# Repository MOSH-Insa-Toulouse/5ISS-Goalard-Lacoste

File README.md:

# Microcontrollers & Open Source Hardware (M&OSH)
This repository contains all the work and related documents realised by Rémi and David as part of the "Microcontroller & Open Source Hardware" major.  
Here is what you can find in this file :
* Course objectives
* Project description
* Technical realisation
* Delivery
* Improvements
* Conclusion
  
## Course objectives
The main objective of this class is to provide a transversal perspective of the creation of an IoT system. From the solution proposal to the end of system design, we take a look at all the conception steps, trying to merge both the hardware and software requirements.

## Project desciption
This project is a multidisciplinary work built around the use of a gas sensor. The idea is the following : we conceived a gas sensor to monitor air quality, and now want to integrate it in on an electronic card (Arduino) to collect data from its environment, then send them over a low speed network.
This is an overview of the architecture :

As it is multidisciplinary, we divided the project in various steps : 
* Gas sensor conception
* Data communication via LoRa
* Hardware & PCB design

## Technical realisation
Let's look at the different steps of the project through the technical realisation point of view.

### Gas sensor conception
The gas sensor designed for monitoring air quality is composed of two sensing elements. Both are based on a combination of silicon substrate with tungsten trioxide nanoparticles, and allow to detect gas concentration regarding the variation of their conductivity. The sensor also integrate a temperature sensor, and only need a few mA to work.   

The sensor parts are described in the following schema :  

For all the sensor information, please refer to the [datasheet](https://github.com/patatorfr/5ISS-Goalard-Lacoste/blob/main/Datasheet/Datasheet.pdf).

The gas sensor was conceived in AIME in october, but we will use a commercial sensor in the next steps of the project for simplicity reasons.    

### Data communication via LoRa
Now we have a working sensor, we want to be able to send the retrieved data. To do so, we will use LoRa protocol and the gateway accessible at INSA via ChirpStack.
In order to achieve the communication, we need a few elements :
* Electonical card (Arduino UNO)
* LoRa communication module (RN2483), plugged to the UNO
* Gas sensor (MQ2), plugged to the UNO
  
First, we use the RN2483 datasheet and choose the pins to use to connect it to the Arduino UNO :

The chosen pins are welded, then the module is connected to the arduino using wires and a breadboard :

To send data using LoRa from the INSA, we have to use a gateway accessible through ChirpStack framework. We reuse an already existing Arduino code modified as follow :
* Connect to the gateway using our specific credentials
* Retrieve data measured by the gas sensor
* Encode data from the sensor as bytes
* Use 'TheThingsNetwork' library, that allows to send data to ChirpStack gateway as bytes

You can find the Arduino code [here](https://github.com/patatorfr/5ISS-Goalard-Lacoste/blob/main/Capteur_Gaz/Capteur_Gaz.ino).

Now the data from the gas sensor can be send out using the gateway, the last step is to make the emitted data accessible. To do it, we use Node-RED and retrieve the data sent from ChirpStack as MQTT packets. We therefore use a function to decode the received data, as ChirpStack send them using base 64, and post a text of the final value : 

To test our system, we displayed the value measured by the sensor in the Arduino IDE, and displayed the same value after getting it on Node-RED. We fortunately displayed twice the same value.

### Hardware & PCB design
In the previous part, we used a breadboard to connect the sensor to the Arduino. This is not an optimal solution, so we use KiCad to design a shield that can be directly plugged on the Arduino board.  

First, let's have a look at the various components of the shield :   

* Arduino UNO board :   
  Generic board provided by KiCad.
  
* Gas sensor :    
  We created a symbol for our manufactured gas sensor, using the 'Package_TO_SOT_THT:TO-5-10_Window' footprint.
  
* Gas type switch :     
  As the gas sensor is capable of measuring 2 different gases, we use a switch to choose the one we want the informations from. It is composed of 2 resistors and a MOSFET transistor. The choice of the gas measured is done via the GPIO n°2 of the Arduino UNO.
     
* LoRa connector :   
  We welded the LoRa module on a little PCB to have a better view/use of its pins. Therefore we just have to plug it on a connector to access the LoRa chip.
  
* Amplifier circuit :   
  This circuit is build based on LTC1050 operational amplifier, a few resistors and capacitors, and a variable resistor.
  
* Variable resistor :      
  As our sensor contains an intern heating resistor, we need to use a variable resistor to adapt the input current and assure it stay in the same range (not to low so the ADC can see it, but not too high so we don't kill the Arduino). The resistor is controlled 
  directly from the Arduino, which allows us to know the 'transformation' done to the current. Using it, we assure a proper functioning of the Arduino, and are still able to provide a good measurement of the gas concentration.

As the sensor resistance is huge, and it varies depending on the gas it measures and its concentration, the input current of the Arduino will be very low. To make it usable, we need to increase the current value, which will be done using an amplifier circuit.

 It is composed as follow :
 
* Low-pass filter for input current noise : R4 - C1
* Actif filter to reduce 50Hz noise : R3 - C4
* Output low-pass filter : R5 - C2
* [Gas sensor](https://github.com/patatorfr/5ISS-Goalard-Lacoste/blob/main/images/image8.png) : we create a component that represent it with the relation => I=V(cp,cn)*(10n+v(gc,gn)*10n)).

We use LTSpice to simulate the behavior of the system and find the cutoff frequency of each filter :

| Filter | Frequency |
|----------|----------|
| 1 [simulation](https://github.com/patatorfr/5ISS-Goalard-Lacoste/blob/main/images/16hz.png) | 16 Hz |
| 2 [simulation](https://github.com/patatorfr/5ISS-Goalard-Lacoste/blob/main/images/1.6hz.png) | 1.6 Hz |
| 3 [simulation](https://github.com/patatorfr/5ISS-Goalard-Lacoste/blob/main/images/1.6khz.png) | 1.6 kHz |

The second step is to build the PCB of the shield using these components. As we were supposed to use INSA's equipement to print the PCB, our constraint was to use only one layer.  

Here is the final version of our PCB :  

And the 3D view to have a better space representation of the PCB :  

## Delivery
A short explanation about the files you can find in the various subdirectories :
* Gas sensor datasheet [here](https://github.com/patatorfr/5ISS-Goalard-Lacoste/blob/main/Datasheet/Datasheet.pdf).
* Arduino code used to retrieve the gas sensor measurements and send them to the gateway [here](https://github.com/patatorfr/5ISS-Goalard-Lacoste/blob/main/Capteur_Gaz/Capteur_Gaz.ino).
* Node-RED flow used to intercept the data reissued from ChirpStack [here](https://github.com/patatorfr/5ISS-Goalard-Lacoste/blob/main/Node-RED/flows.json).
* LTSpice simulations [here](https://github.com/patatorfr/5ISS-Goalard-Lacoste/tree/main/LTSpice).
* KiCad schematic & PCB [here](https://github.com/patatorfr/5ISS-Goalard-Lacoste/tree/main/MyPCB).

## Improvements
These are a few ideas we had to improve our system but couldn't find time to do :
* Node-RED :  we display the data, but we could use existing dashboards to get a better view of gas concentrations.
* PCB :  improve the design, take less space, reduce energy loss and so on.
* Potentiometer control : write some code to control the potentiometer from the arduino, to get closer to real use.
* Sensor programming : write some code to control the sensor, do the calibration, gas recognition... => make it as autonomous as possible.
* End-to-end test : print the PCB, weld all the components and use it in a real applicatio, from data collection to retrieving via Node-RED.
* Energy concumption : we followed the already existing path for the project, but we could take each step to look at the various components/electronic cards used and think about if they are or not the best in term of energy concumption. We could even go further and ask ourselves if there is a better alternative to do the gas measurements than the approach we implemented in this system.

## Conclusion
At the end of this class, we don't have a fully working gas sensor system, even less an optimized one. But it doesn't matter, because the real goal is not so much the complete realization of the project, but rather the global and multidisciplinary vision that it offers us. 

For this work, we had to dive into both the hardware and software parts, and carry them out with their constraints while keeping in mind those of the overall project. This is not something usual, because on a more traditional project we limit ourselves to carrying out our own tasks without looking at what happens during the other stages of the process. As a result, this experience was a good opportunity to expand our capacity to do our part of the work while remembering it can have an impact on the others job, and how to not harden their jobs !

Of course, we also built or consolidated various concepts : 
* Electronical circuit design (LTSpice / KiCad).
* PCB design (KiCad).
* Arduino coding.
* LoRa communication protocol usage.
* Node-RED.
* Even welding !

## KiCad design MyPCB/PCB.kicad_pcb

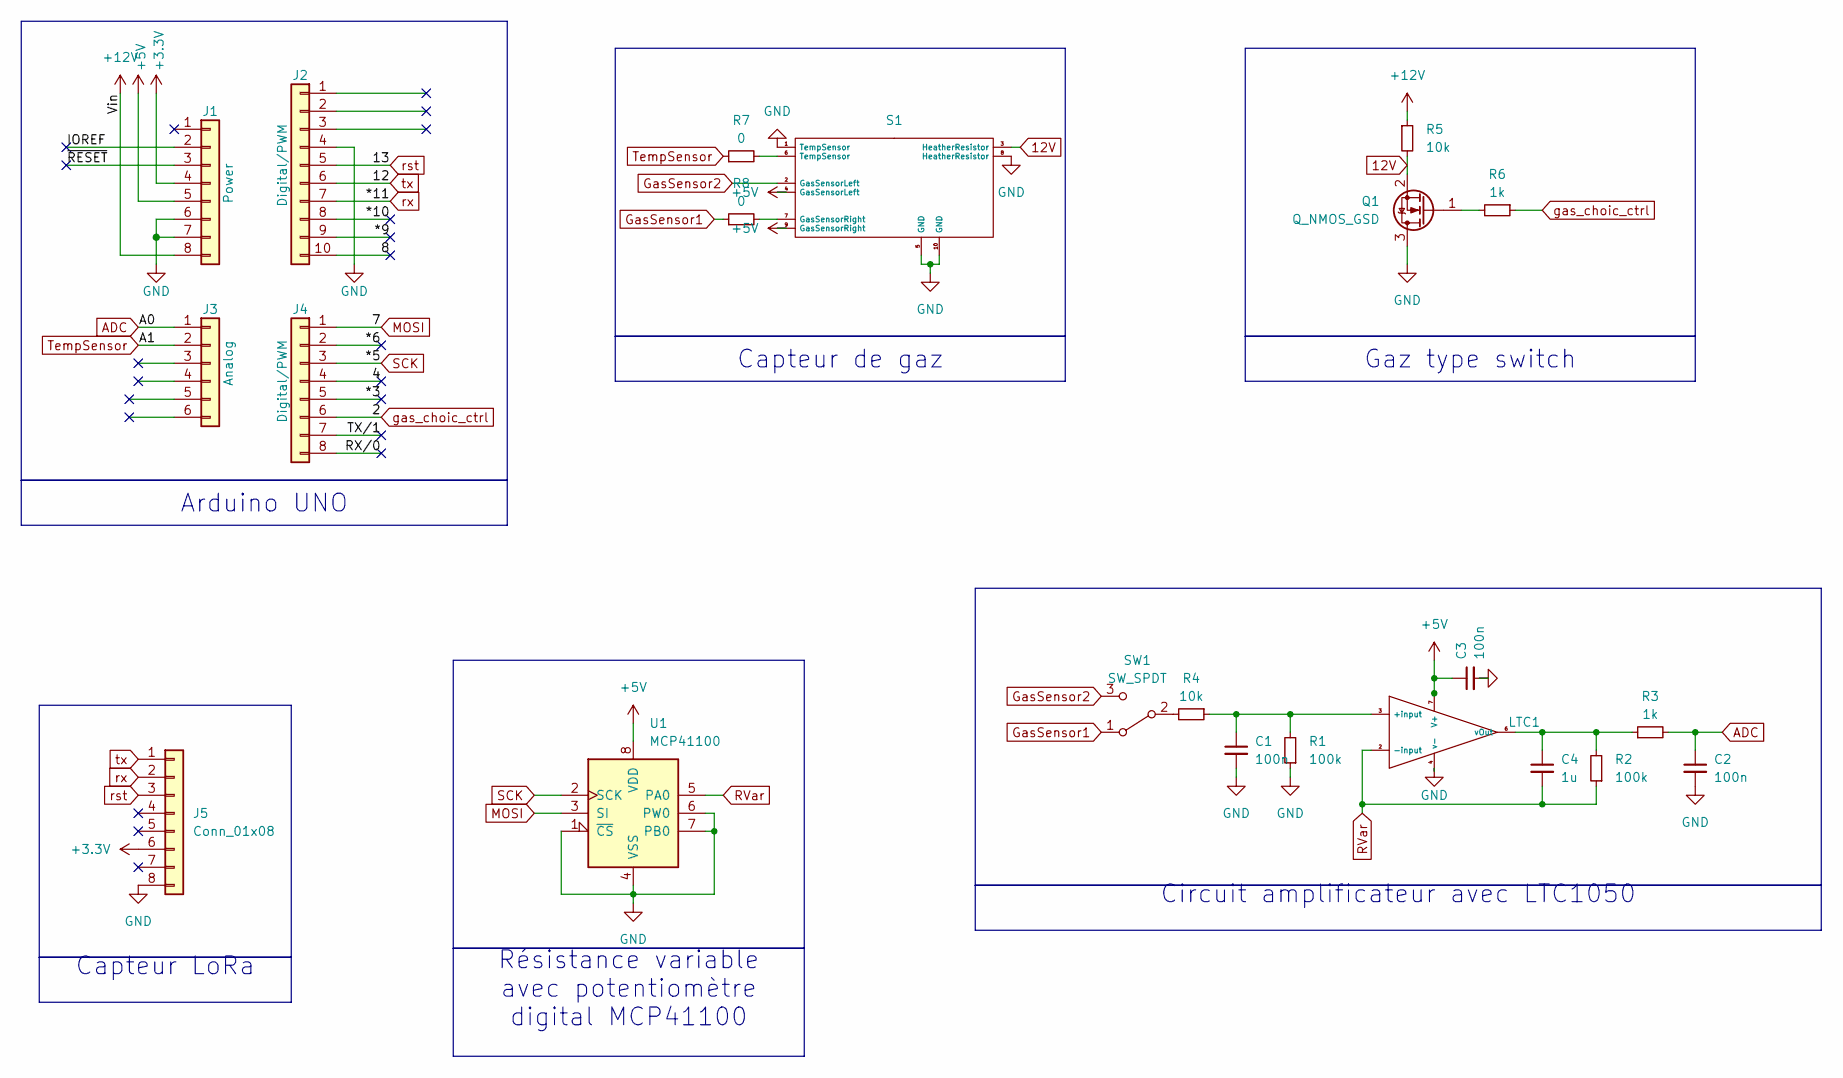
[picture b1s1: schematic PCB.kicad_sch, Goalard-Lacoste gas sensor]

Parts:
C1, C2, C3: 100n; C_Disc_D3.0mm_W1.6mm_P2.50mm
C4: 1u; C_Disc_D3.0mm_W1.6mm_P2.50mm
J1: Power; PinSocket_1x08_P2.54mm_Vertical
J2: Digital/PWM; PinSocket_1x10_P2.54mm_Vertical
J3: Analog; PinSocket_1x06_P2.54mm_Vertical
J4: Digital/PWM; PinSocket_1x08_P2.54mm_Vertical
J5: Conn_01x08; PinSocket_1x08_P2.54mm_Vertical
LTC1: DIP-8_W7.62mm_LongPads
Q1: Q_NMOS_GSD; TO-220-3_Vertical
R1, R2: 100k; R_Axial_DIN0204_L3.6mm_D1.6mm_P5.08mm_Horizontal
R3, R6: 1k; R_Axial_DIN0204_L3.6mm_D1.6mm_P5.08mm_Horizontal
R4, R5: 10k; R_Axial_DIN0204_L3.6mm_D1.6mm_P5.08mm_Horizontal
R7, R8: 0; R_Axial_DIN0204_L3.6mm_D1.6mm_P5.08mm_Horizontal
S1: TO-5-10_Window
SW1: SW_SPDT; SW_Push_2P2T_Toggle_CK_PVA2xxH2xxxxxxV2
U1: MCP41100; DIP-8_W7.62mm

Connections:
12V: Q1.2 (S), R5.2, S1.3 (HeatherResistor)
+5V: C3.1, J1.5, LTC1.7 (V+), S1.4 (GasSensorLeft), S1.9 (GasSensorRight), U1.8 (VDD)
+12V: J1.8, R5.1
/4: J4.4
/8: J2.10
/*3: J4.5
/*6: J4.2
/*9: J2.9
/*10: J2.8
/IOREF: J1.2
/RX/0: J4.8
/TX/1: J4.7
/~RESET: J1.3
ADC: C2.1, J3.1, R3.2
GND: C1.2, C2.2, C3.2, J1.6, J1.7, J2.4, J5.8, LTC1.4 (v-), Q1.3 (D), R1.1, S1.1 (TempSensor), S1.5 (GND), S1.8 (HeatherResistor), S1.10 (GND), U1.1 (~CS), U1.4 (VSS), U1.6 (PW0), U1.7 (PB0)
GasSensor1: R8.1, SW1.1 (A)
GasSensor2: S1.2 (GasSensorLeft), SW1.3 (C)
MOSI: J4.1, U1.3 (SI)
unnamed: C1.1, LTC1.3 (+input), R1.2, R4.1
unnamed: C4.1, LTC1.6 (vOut), R2.2, R3.1
unnamed: Q1.1 (G), R6.2
unnamed: R7.2, S1.6 (TempSensor)
unnamed: R8.2, S1.7 (GasSensorRight)
unnamed: R4.2, SW1.2 (B)
RVar: C4.2, LTC1.2 (-input), R2.1, U1.5 (PA0)
SCK: J4.3, U1.2 (SCK)
TempSensor: J3.2, R7.1
gas_choic_ctrl: J4.6, R6.1
rst: J2.5, J5.3
rx: J2.7, J5.2
tx: J2.6, J5.1

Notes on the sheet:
Capteur de gaz
Circuit amplificateur avec LTC1050
Capteur LoRa
Résistance variable avec potentiomètre digital MCP41100
Arduino UNO
Gaz type switch

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
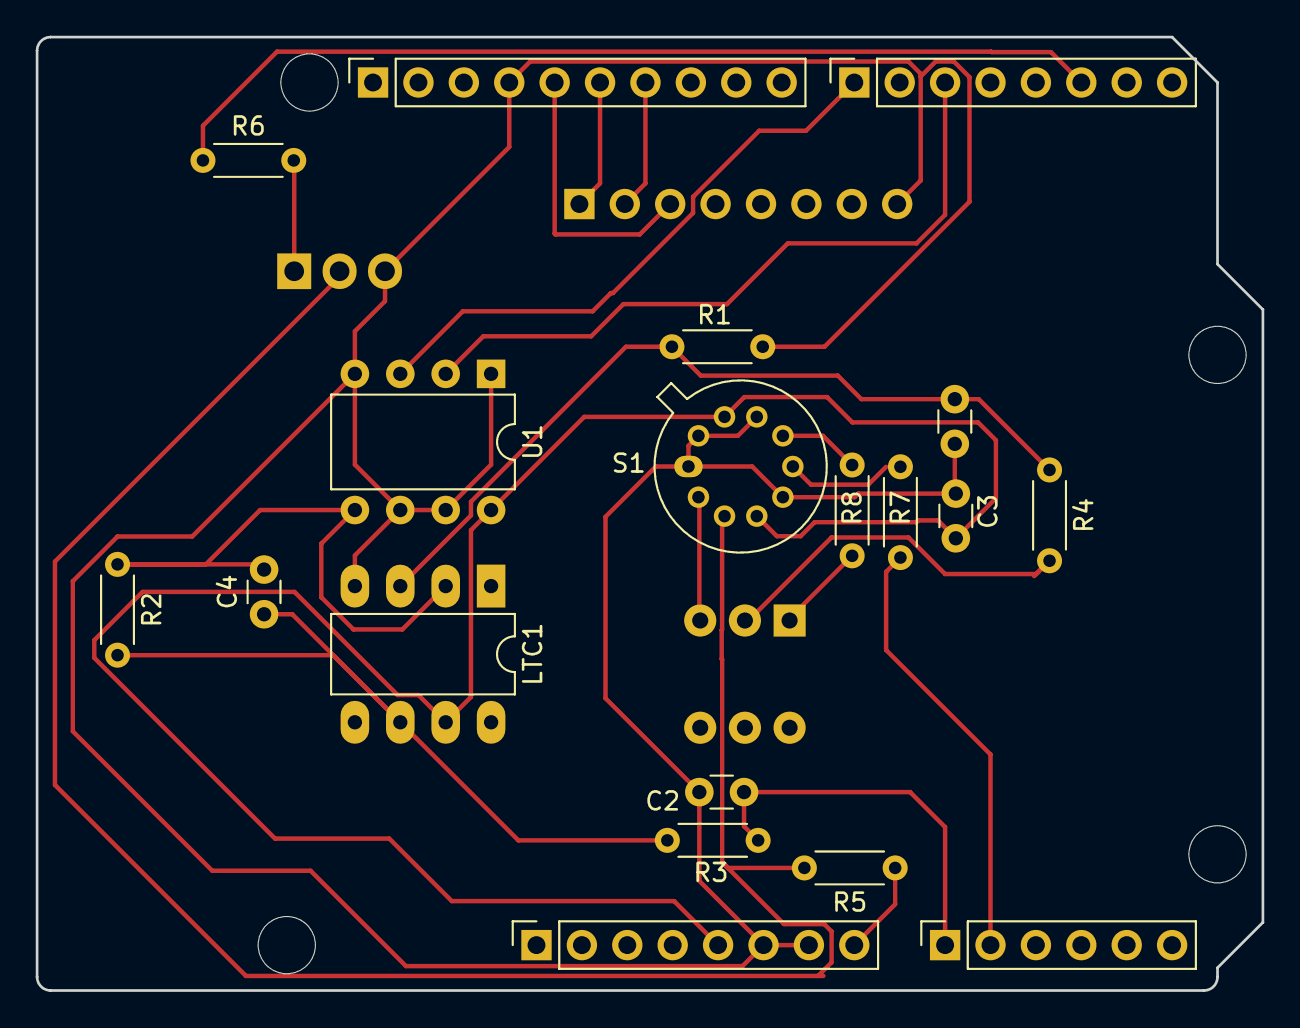
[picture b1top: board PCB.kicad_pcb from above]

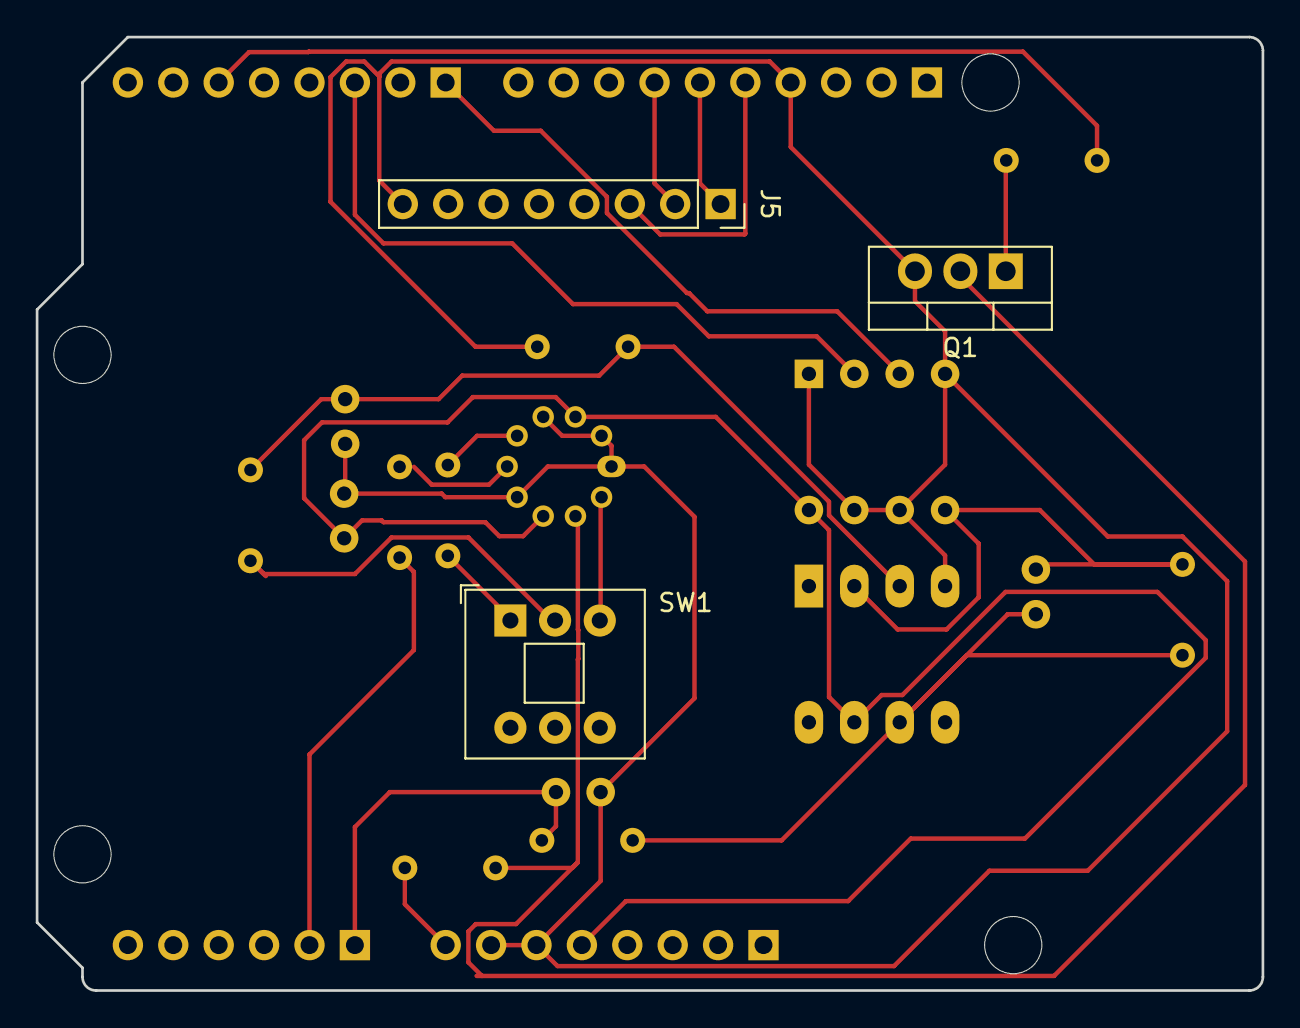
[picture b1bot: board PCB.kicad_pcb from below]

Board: 2 copper layers, 68.6 x 53.3 mm, 26 parts (3 on the bottom side), 21 nets.

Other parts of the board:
MH1, MH2, MH3, MH4: MountingHole_3.2mm

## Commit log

2024-01-15 Rename image7.png to image6.png
2024-01-15 Rename image6.png to image4.png
2024-01-15 Rename image4.png to image7.png
